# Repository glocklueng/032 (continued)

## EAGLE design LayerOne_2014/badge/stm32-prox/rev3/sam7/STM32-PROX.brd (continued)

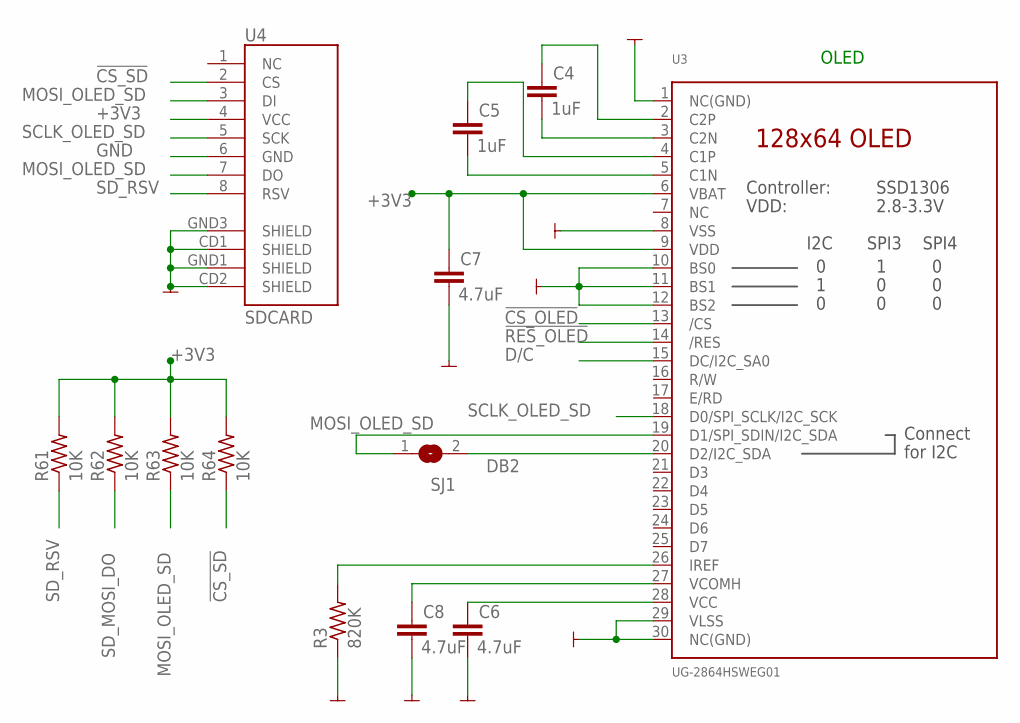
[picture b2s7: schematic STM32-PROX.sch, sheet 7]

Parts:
C4, C5: 1uF; RLC_0603; MPN CC0603ZRY5V7BB105; DIGIKEY 311-1372-2-ND
C6, C7, C8: 4.7uF; RLC_0603; MPN CL10A475KO8NNNC; DIGIKEY 1276-1784-2-ND
R3: 820K; RLC_0603; MPN RC0603JR-07820KL; DIGIKEY 311-820KGRTR-ND
R61, R62, R63, R64: 10K; RLC_0603; MPN RMCF0603JT10K0; DIGIKEY RMCF0603JT10K0CT-ND
SJ1: SOLDERJUMPERREFLOW; SOLDERJUMPER_REFLOW; MPN NONE
U3: UG-2864HSWEG01; MICROBUILDER_UG-2864HSWEG01_0.96IN_WRAPAROUND; PARTNO *
U4: SDCARD; MICRO-SD-SOCKET-PP; PARTNO *

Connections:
!CS_OLED: U3.13 (/CS); also elsewhere on the board
!CS_SD: R64.1, U4.2 (CS); also elsewhere on the board
!RES_OLED: U3.14 (/RES); also elsewhere on the board
D/C: U3.15 (DC/I2C_SA0); also elsewhere on the board
DB2: SJ1.2, U3.20 (D2/I2C_SDA)
MOSI_OLED_SD: R63.1, SJ1.1, U3.19 (D1/SPI_SDIN/I2C_SDA), U4.3 (DI), U4.7 (DO); also elsewhere on the board
unnamed: C4.1, U3.2 (C2P)
unnamed: C4.2, U3.3 (C2N)
unnamed: C5.1, U3.4 (C1P)
unnamed: C5.2, U3.5 (C1N)
unnamed: C8.1, U3.27 (VCOMH)
unnamed: C6.1, U3.28 (VCC)
unnamed: R3.2, U3.26 (IREF)
SCLK_OLED_SD: U3.18 (D0/SPI_SCLK/I2C_SCK), U4.5 (SCK); also elsewhere on the board
SD_MOSI_DO: R62.1; also elsewhere on the board
SD_RSV: R61.1, U4.8 (RSV)

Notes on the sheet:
OLED

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
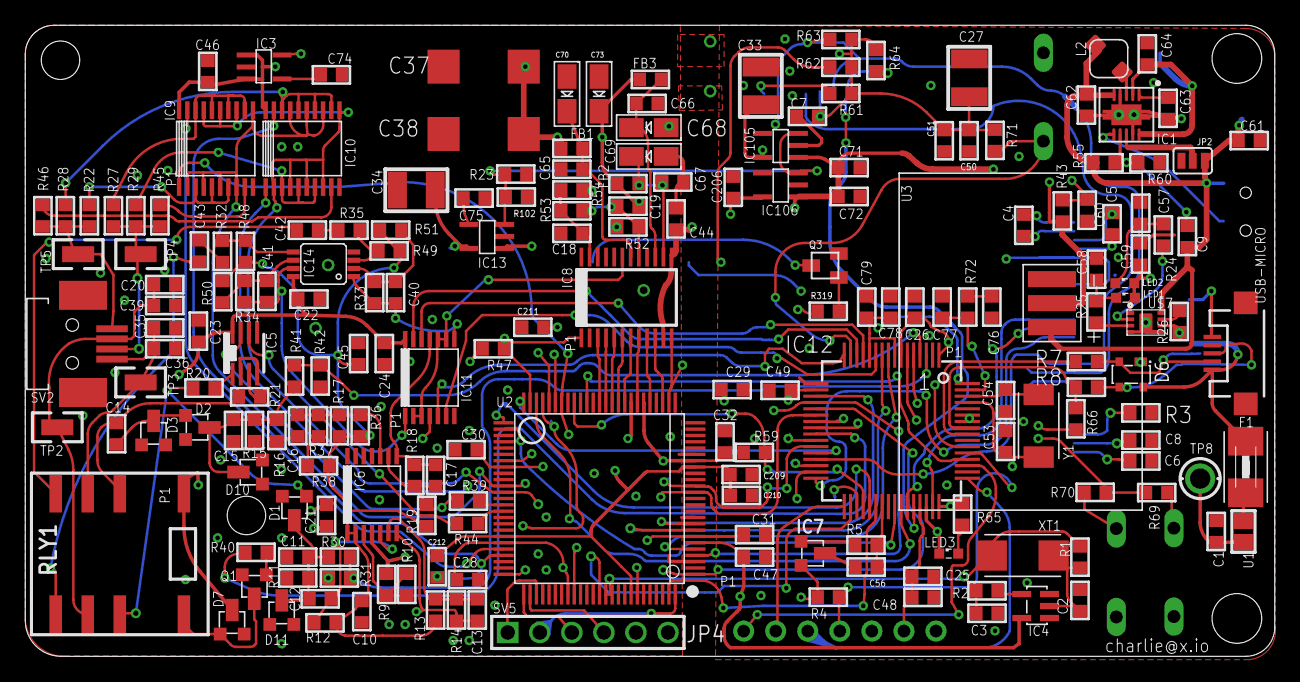
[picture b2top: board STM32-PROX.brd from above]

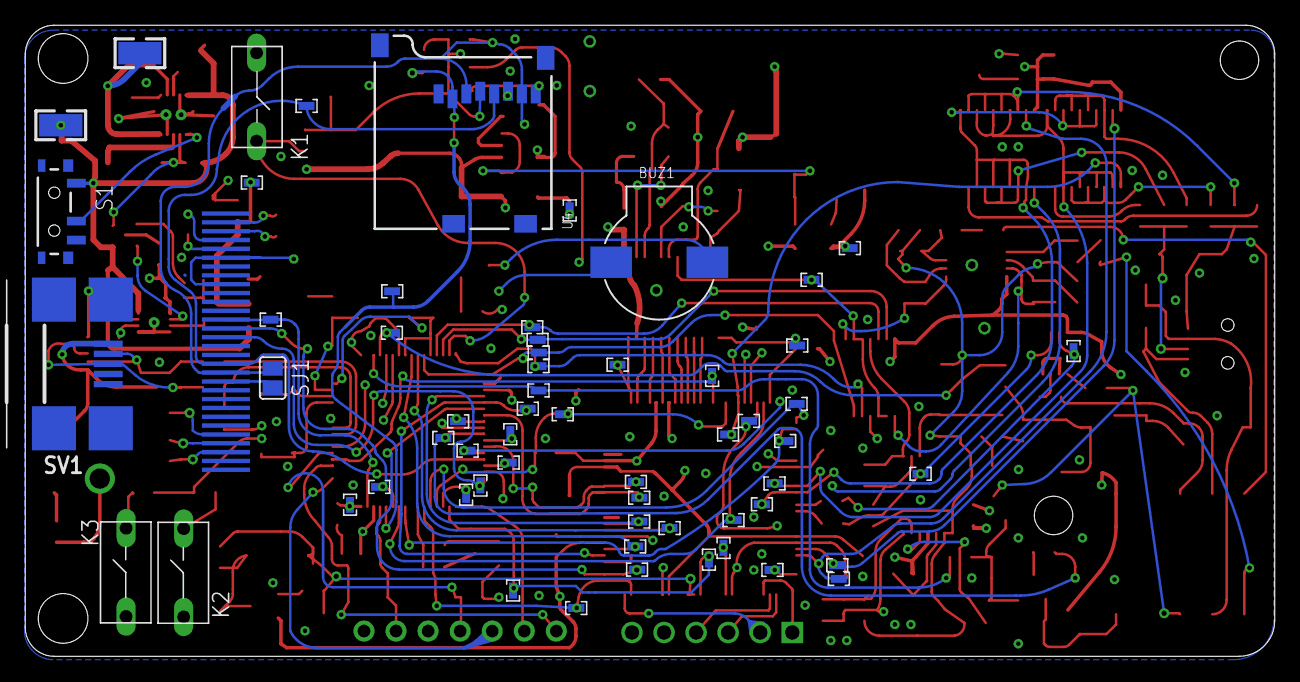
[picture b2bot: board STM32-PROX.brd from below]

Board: 4 copper layers, 99.0 x 50.0 mm, 264 parts (59 on the bottom side), 160 nets.

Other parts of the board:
C9: 100nF; RLC_0603
F1: 1812
K1, K2, K3: B3F-5XX
TP8: TESTPADKEYSTONE-PTH; KEYSTONE-PTH-TESTPOINT-5011
U$1, U$2: STAND-OFF-TIGHT
U$11, U$12, U$13: L1LOGO

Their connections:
unnamed 119: C9.2; also elsewhere on the board
SW_K1: K1.2; also elsewhere on the board
SW_K2: K2.2; also elsewhere on the board
SW_K3: K3.2; also elsewhere on the board
VBUS: TP8.A; also elsewhere on the board

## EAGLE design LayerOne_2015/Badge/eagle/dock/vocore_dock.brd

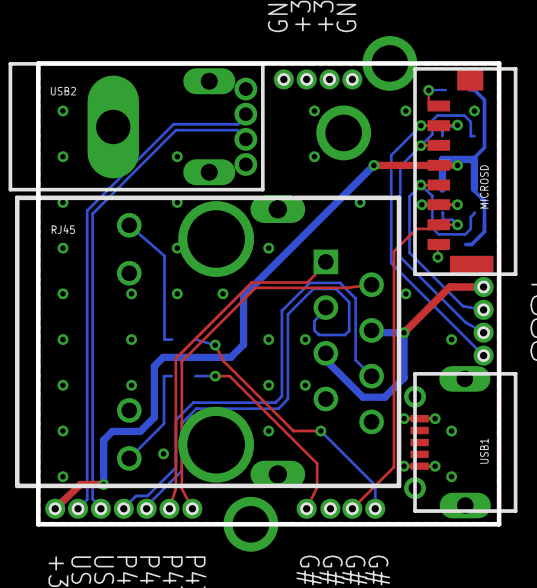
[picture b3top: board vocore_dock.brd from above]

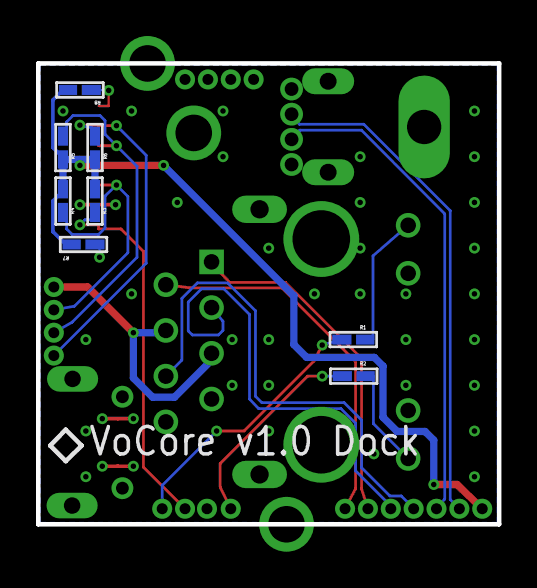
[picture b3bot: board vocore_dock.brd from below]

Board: 4 copper layers, 25.6 x 25.6 mm, 34 parts (8 on the bottom side), 20 nets.

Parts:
HOLE1, HOLE2, HOLE3: HOLE_80MIL; HOLE_80MIL_1PRIMARY
MICROSD: MICROSD_PADS; MICROSD_PADS_1PRIMARY
PB04, PB05, PB06, PB07, PB12, PB13, PB14, PB15, PB16, PB17, PB18: PORT_1PIN_DECAL; PORT_1PIN_DECAL_1PRIMARY
PL05, PL06, PL07, PL08: PORT_1PIN_DECAL; PORT_1PIN_DECAL_1PRIMARY
PT01, PT02, PT03, PT04: PORT_1PIN_DECAL; PORT_1PIN_DECAL_1PRIMARY
R1, R2, R3, R4, R5, R6, R7, R8: 0402_L; 0402_L_1PRIMARY
RJ45: RJ45ALED; RJ45ALED_1PRIMARY
USB1: USB_MICRO_A; USB_MICRO_A_1PRIMARY
USB2: USB_FULL_TALL; USB_FULL_TALL_1PRIMARY

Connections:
+1.8V: PL05.1, RJ45.4, RJ45.5
+3.3V: MICROSD.4, PB18.1, R3.2, R4.2, R5.2, R6.2, R7.2, R8.2
+5V: PT02.1, PT03.1, USB1.1, USB2.1
GND: MICROSD.6, PT01.1, PT04.1, RJ45.10, RJ45.12, USB1.4, USB2.4
LED_G: R1.2, RJ45.9
LED_Y: R2.2, RJ45.11
P4RN: PB15.1, RJ45.6
P4RP: PB14.1, RJ45.3
P4TN: PB12.1, RJ45.2
P4TP: PB13.1, RJ45.1
SPI_CLK: MICROSD.5, PL06.1, R4.1
SPI_CS1: MICROSD.2, PL08.1, R6.1
SPI_MISO: MICROSD.7, PB05.1, R3.1
SPI_MOSI: MICROSD.3, PL07.1, R5.1
SPI_RSV1: MICROSD.8, R7.1
SPI_RSV2: MICROSD.1, R8.1
UARTF_DTR: PB07.1, R2.1
UARTF_RXD: PB04.1, R1.1
USB_M: PB16.1, USB2.2
USB_P: PB17.1, USB2.3

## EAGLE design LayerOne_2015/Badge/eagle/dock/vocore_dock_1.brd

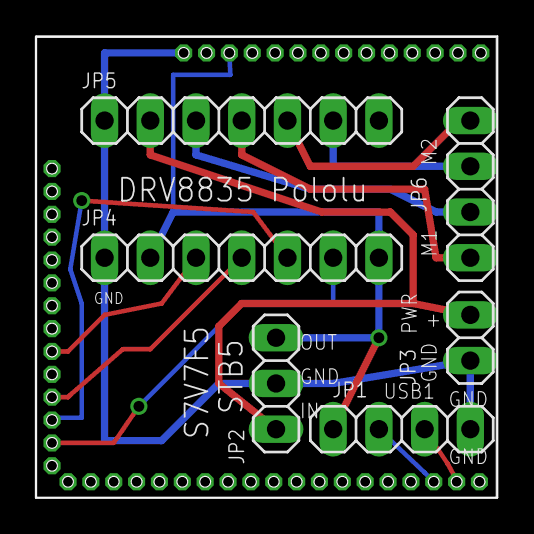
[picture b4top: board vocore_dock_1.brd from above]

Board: 2 copper layers, 25.7 x 25.7 mm, 7 parts (0 on the bottom side), 13 nets.

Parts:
JP1: USB1; 1X04
JP2: STB5; 1X03
JP3: PWR; 1X02
JP4, JP5: 1X07
JP6: 1X04
U$1: VOCORE_SHIELD; VOCORE_DOC_CUSTOM

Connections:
unnamed: JP1.1, JP2.2, JP3.2, JP4.1, JP5.1, U$1.GND2
unnamed: JP2.3, JP3.1, JP5.2
unnamed: JP1.4, JP2.1, JP4.2, JP4.7, U$1.+6.0VIN1
unnamed: JP4.3, U$1.G#23/LED1
unnamed: JP1.3, U$1.USB-
unnamed: JP1.2, U$1.USB+
unnamed: JP4.4, U$1.G#24/LED2
unnamed: JP4.5, U$1.G#25/LED3
unnamed: JP4.6, U$1.G#26/LED4
unnamed: JP5.4, JP6.1
unnamed: JP5.3, JP6.2
unnamed: JP5.5, JP6.4
unnamed: JP5.6, JP6.3

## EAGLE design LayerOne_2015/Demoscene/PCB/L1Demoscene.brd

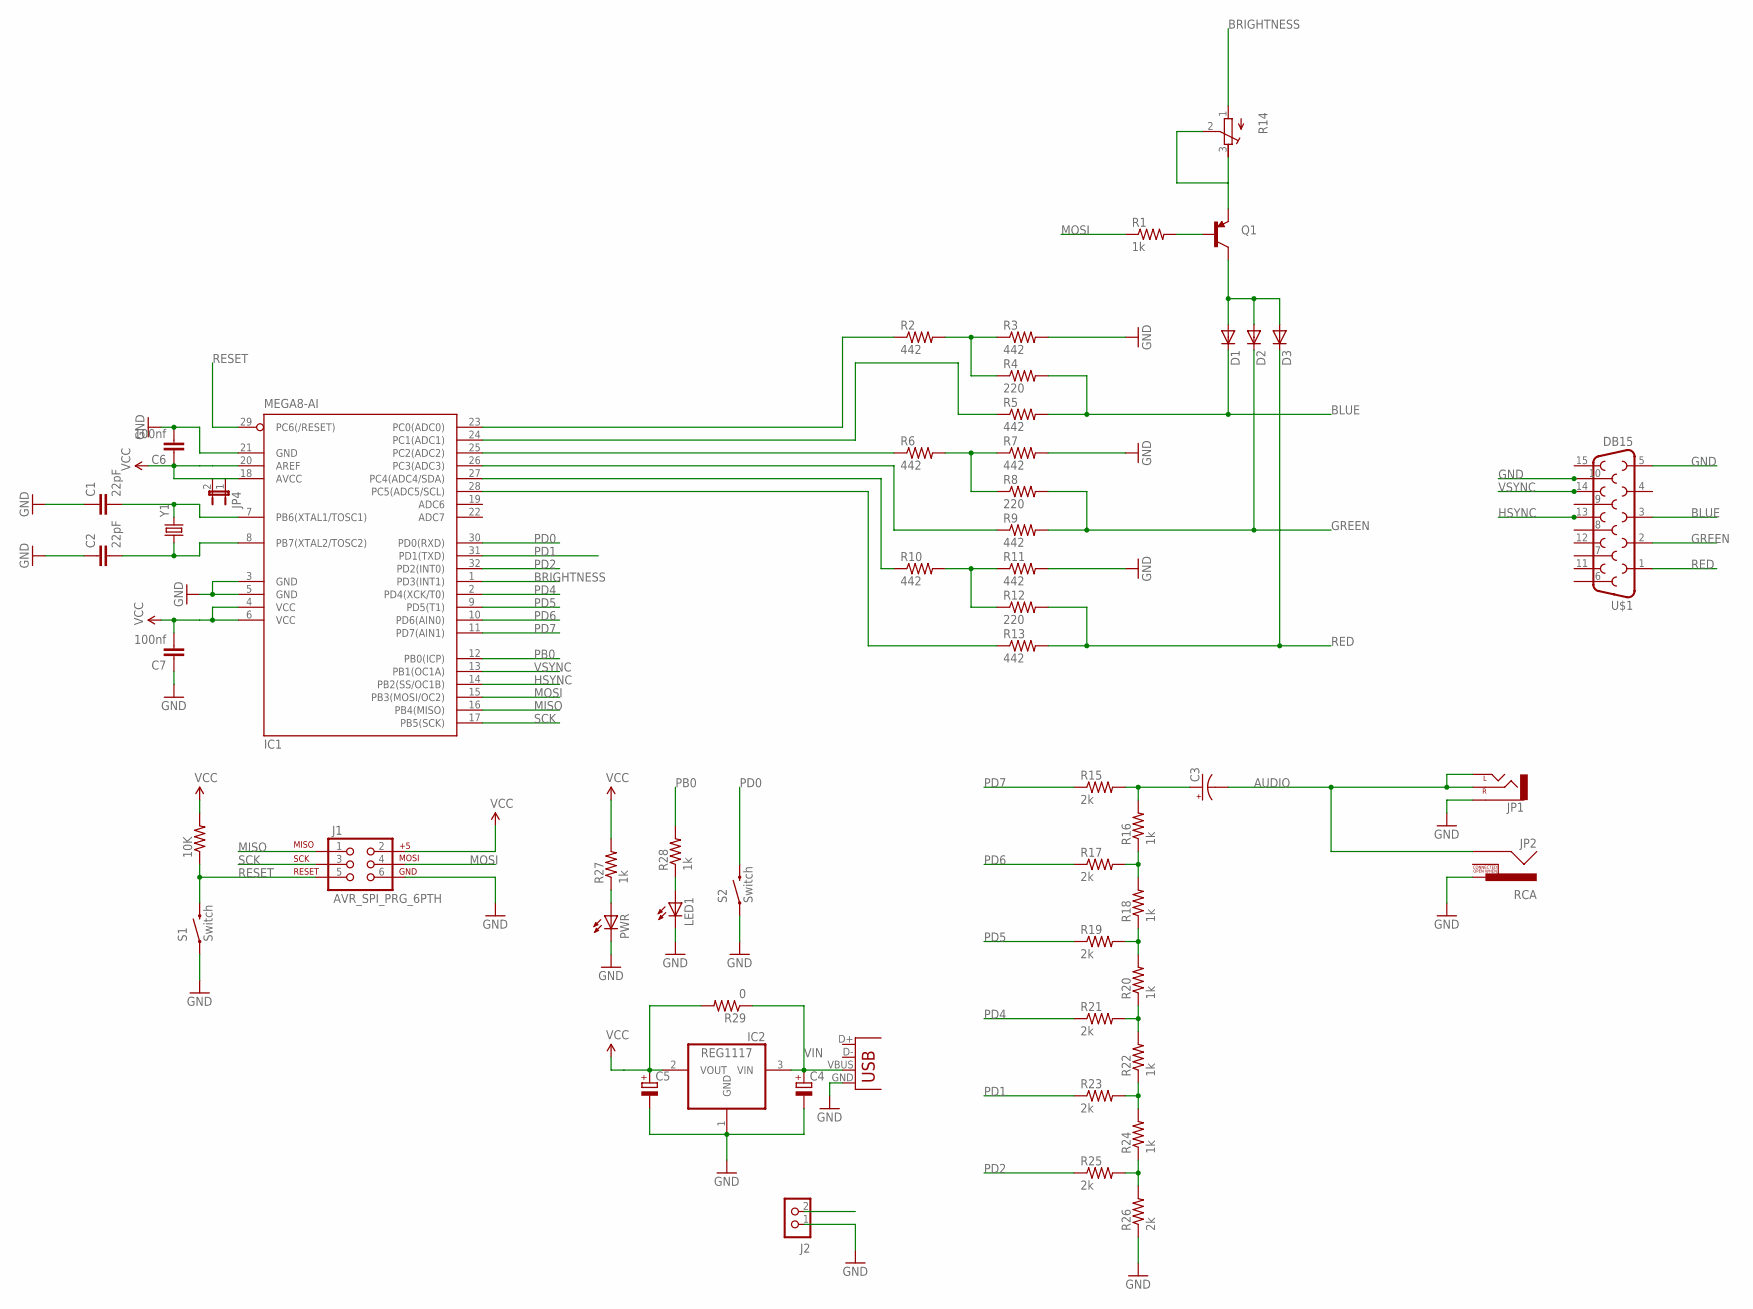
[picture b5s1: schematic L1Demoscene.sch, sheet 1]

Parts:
10K: RESISTOR0603-RES; 0603-RES
C1, C2: 22pF; 0603-CAP
C3: CAP_POL1206; EIA3216
C4, C5: CAPACITOR_POL-SMC_A; SMC_A
C6, C7: 100nf; 0603-CAP
D1, D2, D3: DIODESOD; SOD-323
IC1: MEGA8-AI; TQFP32-08
IC2: REG1117; SOT223
J1: AVR_SPI_PRG_6PTH; 2X3
J2: CON_HEADER_1X02-PTH; M1X2
JP1: AUDIO-JACKPTH; AUDIO-JACK
JP2: RCA
JP3: USB-MICROB
JP4: JUMPER-2SMD-NC; SJ_2S
LED1: LED-0603; LED-603
PWR: LED-0603; LED-603
Q1: TRANSISTOR_PNPSMD; SOT23-3
R1, R16, R18, R20, R22, R24, R27, R28: 1k; 0603-RES
R2, R3, R5, R6, R7, R9, R10, R11, R13: 442; 0603-RES
R4, R8, R12: 220; 0603-RES
R14: R-TRIMM3296W; RTRIM3296W
R15, R17, R19, R21, R23, R25, R26: 2k; 0603-RES
R29: 0; 1206
S1, S2: Switch; SPARKFUN-ELECTROMECHANICAL_TACTILE-SWITCH-1101NE
U$1: DB15
Y1: CRYSTALHC49US; HC49US

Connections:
AUDIO: C3.C (-), JP1.RING (RIGHT), JP1.TIP (LEFT), JP2.SHELL
BLUE: D1.1 (C), R4.2, R5.2, U$1.3
BRIGHTNESS: IC1.1 (PD3(INT1)), R14.1 (A)
GND: C1.1, C2.1, C4.-, C5.-, C6.2, C7.1, IC1.3 (GND), IC1.5 (GND), IC1.21 (GND), IC2.1 (GND), J1.6, J2.1, JP1.SLEEVE, JP2.PIN, JP3.GND, LED1.C, PWR.C, R3.2, R7.2, R11.2, R26.1, S1.P$1 (1), S2.P$1 (1), U$1.5, U$1.10
GREEN: D2.1 (C), R8.2, R9.2, U$1.2
HSYNC: IC1.14 (PB2(SS/OC1B)), U$1.13
MISO: IC1.16 (PB4(MISO)), J1.1
MOSI: IC1.15 (PB3(MOSI/OC2)), J1.4, R1.1
unnamed: C1.2, IC1.7 (PB6(XTAL1/TOSC1)), Y1.2
unnamed: C2.2, IC1.8 (PB7(XTAL2/TOSC2)), Y1.1
unnamed: IC1.23 (PC0(ADC0)), R2.1
unnamed: R2.2, R3.1, R4.1
unnamed: D1.2 (A), D2.2 (A), D3.2 (A), Q1.3 (C)
unnamed: Q1.1 (B), R1.2
unnamed: IC1.24 (PC1(ADC1)), R5.1
unnamed: IC1.25 (PC2(ADC2)), R6.1
unnamed: R6.2, R7.1, R8.1
unnamed: PWR.A, R27.1
unnamed: IC1.26 (PC3(ADC3)), R9.1
unnamed: IC1.28 (PC5(ADC5/SCL)), R13.1
unnamed: LED1.A, R28.1
unnamed: IC1.27 (PC4(ADC4/SDA)), R10.1
unnamed: R10.2, R11.1, R12.1
unnamed: Q1.2 (E), R14.2 (S), R14.3 (E)
unnamed: C3.A (+), R15.2, R16.2
unnamed: R16.1, R17.2, R18.2
unnamed: R18.1, R19.2, R20.2
unnamed: R20.1, R21.2, R22.2
unnamed: R22.1, R23.2, R24.2
unnamed: R24.1, R25.2, R26.2
PB0: IC1.12 (PB0(ICP)), R28.2
PD0: IC1.30 (PD0(RXD)), S2.P$2 (2)
PD1: IC1.31 (PD1(TXD)), R23.1
PD2: IC1.32 (PD2(INT0)), R25.1
PD4: IC1.2 (PD4(XCK/T0)), R21.1
PD5: IC1.9 (PD5(T1)), R19.1
PD6: IC1.10 (PD6(AIN0)), R17.1
PD7: IC1.11 (PD7(AIN1)), R15.1
RED: D3.1 (C), R12.2, R13.2, U$1.1
RESET: 10K.1, IC1.29 (PC6(/RESET)), J1.5, S1.P$2 (2)
SCK: IC1.17 (PB5(SCK)), J1.3
VCC: 10K.2, C5.+, C6.1, C7.2, IC1.4 (VCC), IC1.6 (VCC), IC1.18 (AVCC), IC1.20 (AREF), IC2.2 (VOUT), J1.2, JP4.1, JP4.2, R27.2, R29.2
VIN: C4.+, IC2.3 (VIN), J2.2, JP3.VBUS, R29.1
VSYNC: IC1.13 (PB1(OC1A)), U$1.14

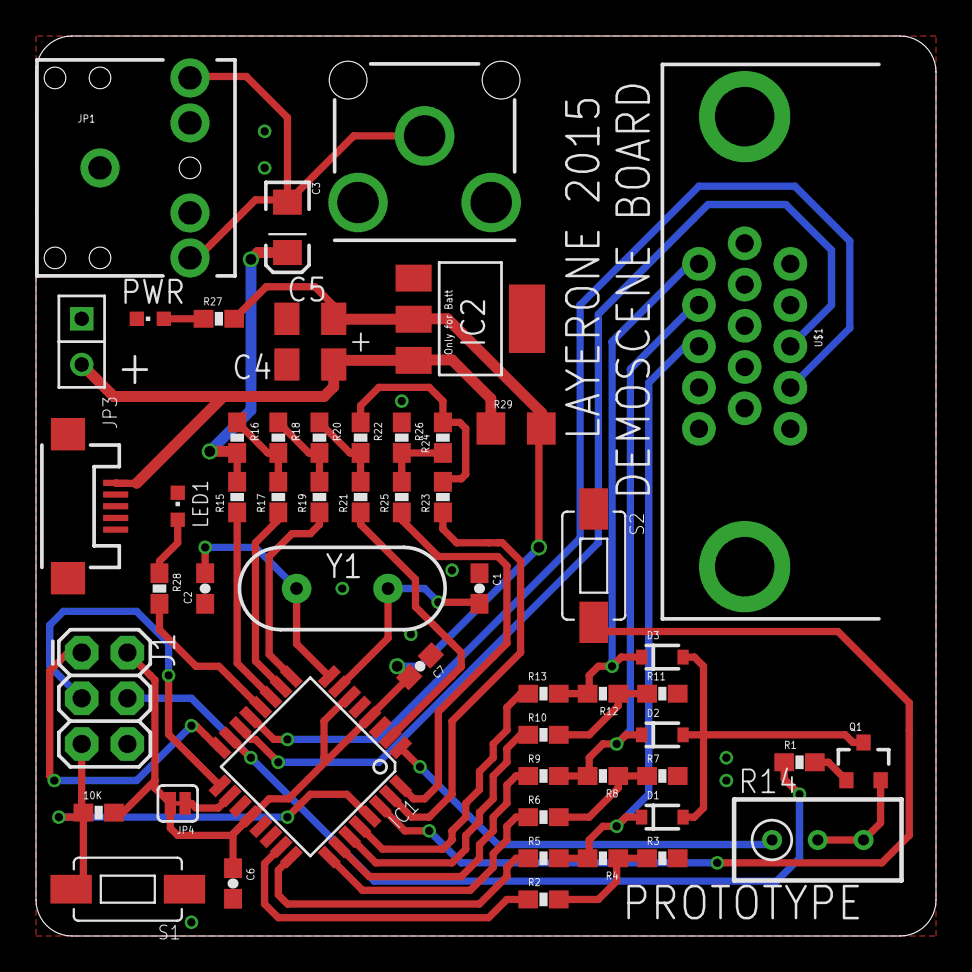
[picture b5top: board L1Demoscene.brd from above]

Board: 2 copper layers, 50.0 x 50.0 mm, 55 parts (0 on the bottom side), 44 nets.
